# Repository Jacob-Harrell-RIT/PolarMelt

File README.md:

# PolarMelt
A meltybrain implementation for teensy3.2 that will (hopefully) use magnetometer data for directional error detection
SBUS Library Source:https://github.com/bolderflight/SBUS

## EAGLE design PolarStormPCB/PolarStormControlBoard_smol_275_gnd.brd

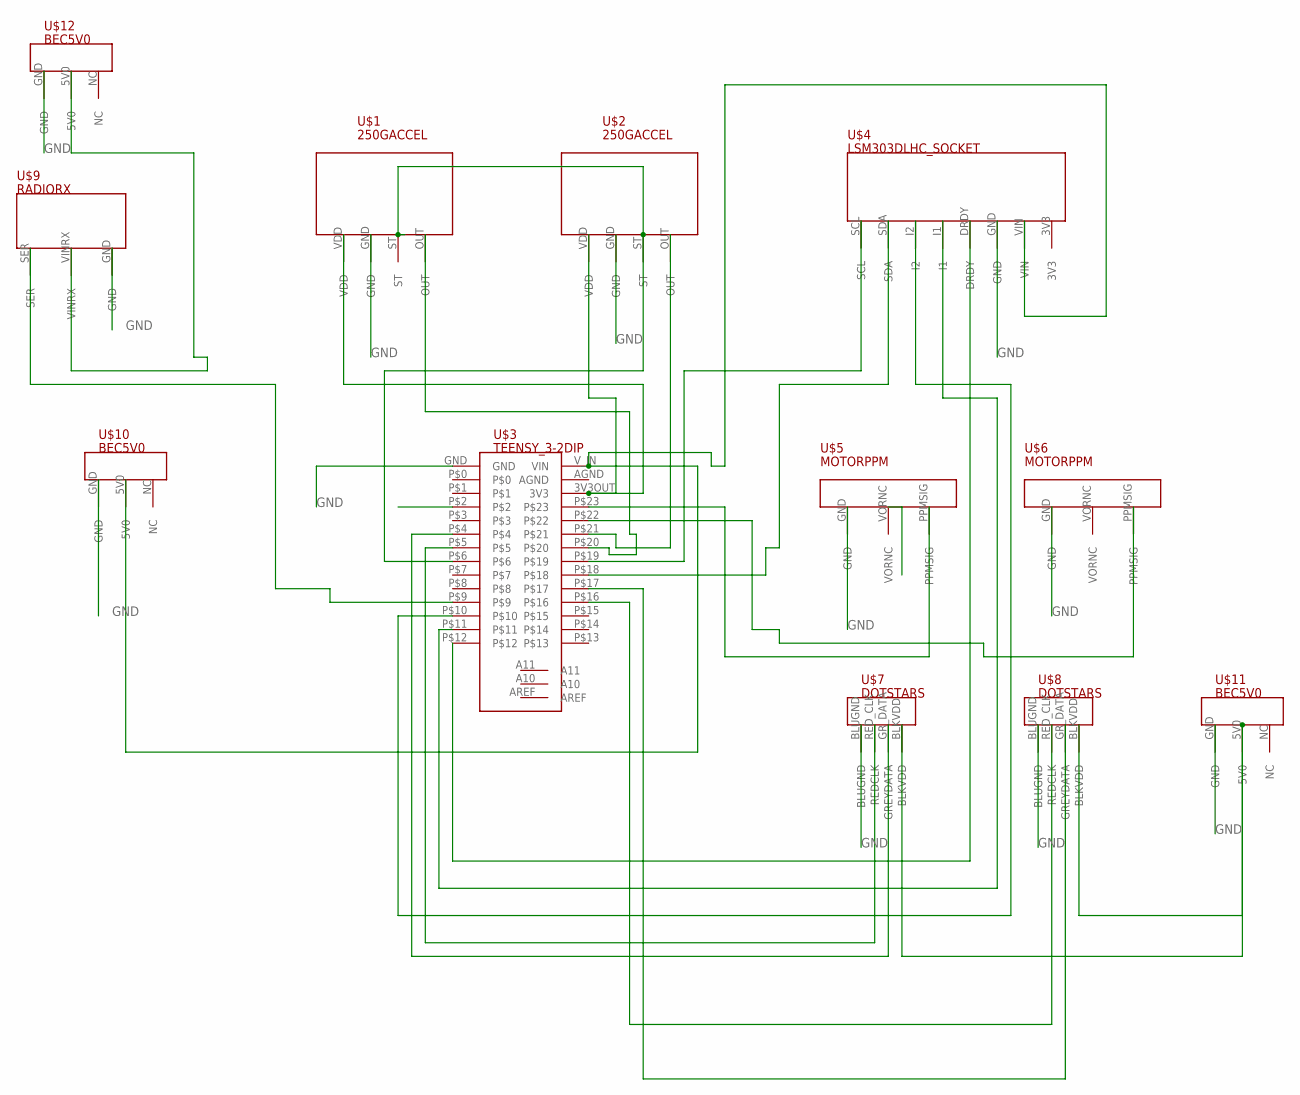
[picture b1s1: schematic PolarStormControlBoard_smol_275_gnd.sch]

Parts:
U$1, U$2: 250GACCEL
U$3: TEENSY_3-2DIP; TEENSY_3_2_SOCKET
U$4: LSM303DLHC_SOCKET
U$5, U$6: MOTORPPM; MOTORINTERFACE
U$7, U$8: DOTSTARS; DOTSTARHEADER
U$9: RADIORX; SERIALRX
U$10, U$11, U$12: BEC5V0; BECIN

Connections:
3V3: U$4.3V3
GND: U$1.GND, U$2.GND, U$3.GND, U$4.GND, U$5.GND, U$6.GND, U$7.BLUGND, U$8.BLUGND, U$9.GND, U$10.GND, U$11.GND, U$12.GND
unnamed: U$2.OUT, U$3.P$21
unnamed: U$1.OUT, U$3.P$20
unnamed: U$1.VDD, U$2.VDD, U$3.3V3OUT (3V3)
unnamed: U$9.VINRX, U$12.5V0
unnamed: U$3.P$23, U$5.PPMSIG
unnamed: U$3.P$22, U$6.PPMSIG
unnamed: U$3.P$9, U$9.SER
unnamed: U$7.BLKVDD, U$8.BLKVDD, U$11.5V0
unnamed: U$3.V_IN (VIN), U$4.VIN, U$10.5V0
unnamed: U$3.P$5, U$7.RED_CLK (REDCLK)
unnamed: U$3.P$4, U$7.GR_DATA (GREYDATA)
unnamed: U$3.P$16, U$8.RED_CLK (REDCLK)
unnamed: U$3.P$17, U$8.GR_DATA (GREYDATA)
unnamed: U$3.P$19, U$4.SCL
unnamed: U$3.P$18, U$4.SDA
unnamed: U$3.P$12, U$4.DRDY
unnamed: U$3.P$11, U$4.I1
unnamed: U$1.ST, U$2.ST, U$3.P$6
unnamed: U$3.P$10, U$4.I2
VORNC: U$6.VORNC

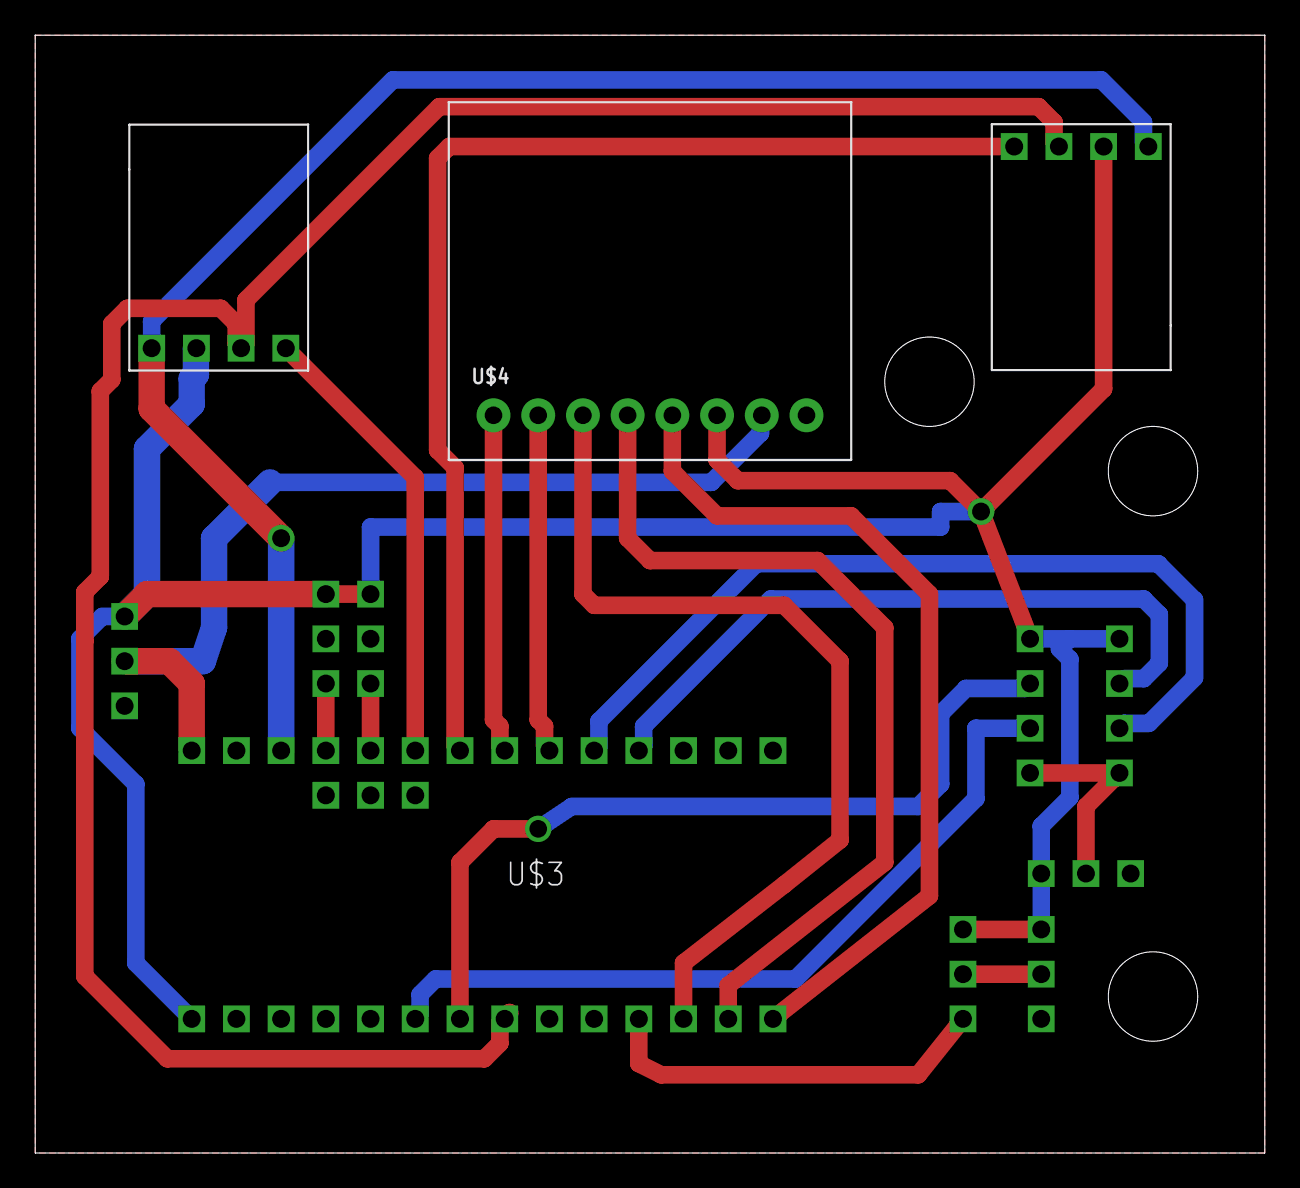
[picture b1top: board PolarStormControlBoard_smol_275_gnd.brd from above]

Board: 2 copper layers, 69.8 x 63.5 mm, 12 parts (0 on the bottom side), 20 nets.

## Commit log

2018-01-31 Addition of POV code
2018-02-09 Add files via upload
    ino files for testing pcb
2018-02-09 Add files via upload
    testing LED and motor functions simultaneously, working on fail safe functionality
2018-02-10 Update SBUS_both_and_LED.ino
    made failsafe actually work
2018-02-12 Create mot_rev
    reverse motors?
2018-02-12 Temporary Modification of Spinning POW
2018-02-12 Create LEDACCEL
2018-02-12 Create sbusbothled_414pm
2018-02-14 Create Accel_Test.ino
    Addition of new file that should now read accelerometer
2018-02-14 Update Spinning_POW.ino
    Addition of starting color and neutral color
2018-02-14 Create POV_Jacob_tmp
    pov code
2018-02-15 Create Accel_With_Config
    Addition of Configuration Mode Checking
2018-02-15 Create POV_With_Config_Alex_tmp
    Non-Final Config Code for the POV
2018-02-16 Create POV_Trans_Config
    POV with Configuration and Translation (?)
2018-02-17 prelim tank drive code
2018-02-17 swappedminus
2018-02-17 swapped control direction and lowered fwd speed
2018-02-17 Update IHopeThisIsTankDrive
2018-02-18 PCB files for Polar storm, eagle good, gcode not
    Note gcode currently has shorts between the magnetometer pins but the eagle files should be ok
2018-03-12 Added PDF and DXF of PCB
    For Reference Only
2018-03-15 Create MAG_Interrupt.ino
    Added a simple interrupt based LSM303 read
2018-03-18 removed y,z for accel removed x for mag
2018-03-18 removed y,z accel reads and x mag read,
    //TODO if mag only asked for 4 bytes it stops sending data
2018-03-18 added thresholding for x data, removed y, z accel, removed x mag
